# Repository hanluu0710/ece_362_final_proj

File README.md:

# ece_362_final_proj
Pocket oscilloscope

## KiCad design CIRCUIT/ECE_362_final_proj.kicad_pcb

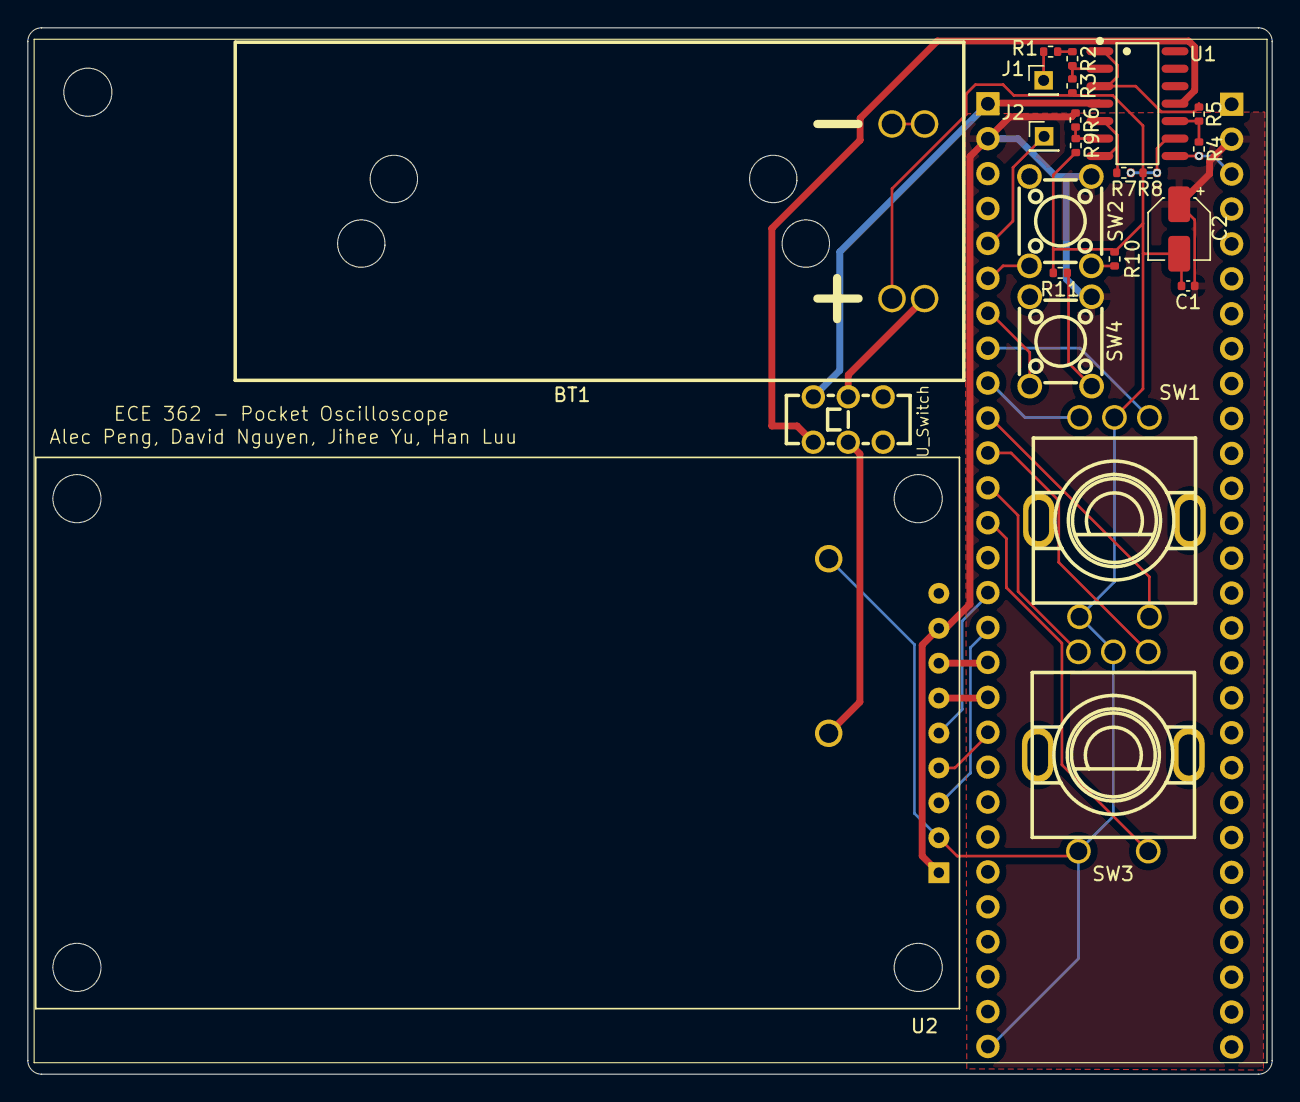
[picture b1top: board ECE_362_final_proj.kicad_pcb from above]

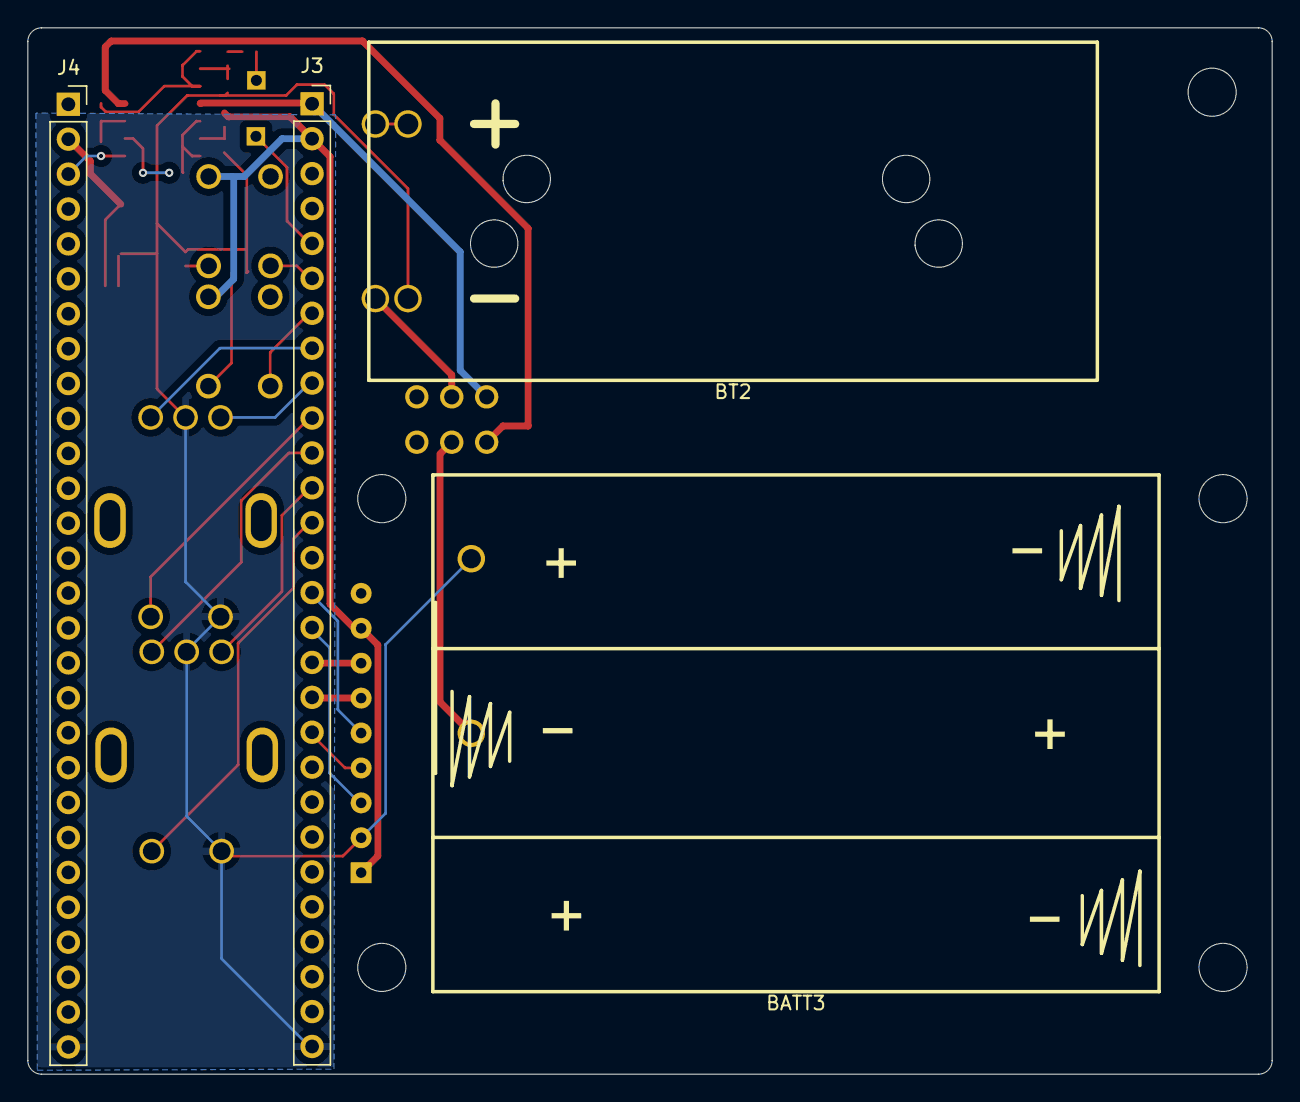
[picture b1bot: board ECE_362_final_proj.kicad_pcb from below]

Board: 2 copper layers, 90.5 x 76.1 mm, 27 parts (4 on the bottom side), 32 nets.

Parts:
BATT3: BAT-TH_2479
BT1, BT2: BAT-TH_2P-L53.0-W24.6-P12.70_2468
C1: .1uF; C_0402_1005Metric
C2: 10uF; CP_Elec_4x4.5
J1, J2: Conn_01x01_Pin; PinHeader_1x01_P2.00mm_Vertical
J3, J4: Conn_01x28_Socket; PinSocket_1x28_P2.54mm_Vertical
R1: 680k; R_0402_1005Metric
R2: 220k; R_0402_1005Metric
R3: 100k; R_0402_1005Metric
R4, R5, R6, R7, R8, R9: 10k; R_0402_1005Metric
R10, R11: 1000; R_0402_1005Metric
SW1, SW3: SW-TH_EC11E18244A5
SW2: BUTTON_MODE; SW-TH_4P-L6.0-W6.0-P4.50-LS6.5
SW4: BUTTON_CAPTURE; SW-TH_4P-L6.0-W6.0-P4.50-LS6.5
U1: TL084; SOP-14_L8.6-W3.9-P1.27-LS6.0-BL
U2: LCD_MSP2202_without_sd
U_Switch: SW-TH_SSSS222700

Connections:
+3.3V: C1.1, C2.1, J3.2, J4.2, R6.1, SW2.4 (A), SW4.4 (A), U2.1, U2.8
+BATT: J3.1, J4.1, U1.4 (V+), U_Switch.1
-BATT: U1.11 (V-), U_Switch.4
/GPIO2: J2.1, J3.5
/GPIO3: J3.6, SW2.1
/GPIO4: J3.7, SW4.1
/GPIO5: J3.8, SW1.A
/GPIO6: J3.9, SW1.B
/GPIO7: J3.10, SW1.D
/GPIO8: J3.11, SW3.A
/GPIO9: J3.12, SW3.B
/GPIO10: J3.13, SW3.D
/GPIO12: J3.15, U2.5
/GPIO13: J3.16, U2.3
/GPIO14: J3.17, U2.7
/GPIO15: J3.18, U2.6
/GPIO16: J3.19, U2.4
/GPIO47_ADC7: J4.3, R4.2, U1.8
BAT3: BATT3.2, U_Switch.5
BT1+: BT1.2, U_Switch.2
BT1_GND: BT1.1, BT2.2
GND: BATT3.1, BT2.1, C1.2, C2.2, J3.28, J4.28, R3.2, R8.2, R9.2, R10.2, R11.2, SW1.C, SW1.E, SW3.C, SW3.E, U2.2
unnamed: J1.1, R1.1
unnamed: R1.2, R2.1
unnamed: R10.1, SW2.3 (K)
unnamed: R11.1, SW4.3 (K)
unnamed: R5.1, U1.1, U1.3 (+)
unnamed: R2.2, R3.1, U1.2 (-)
unnamed: R7.2, U1.5 (+), U1.7
unnamed: R6.2, R9.1, U1.6 (-)
unnamed: R4.1, R5.2, U1.10 (+)
unnamed: R7.1, R8.1, U1.9 (-)

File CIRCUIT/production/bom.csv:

Designator,Footprint,Quantity,Value,LCSC Part #,Customer Supply
,,1,,,
BATT3,BAT-TH_2479,1,BAT-TH_2479,,
"BT1, BT2",BAT-TH_2P-L53.0-W24.6-P12.70_2468,2,BAT-TH_2P-L53.0-W24.6-P12.70_2468,,
C1,0402,1,.1uF,,
C2,CP_Elec_4x4.5,1,10uF,,
"J1, J2",PinHeader_1x01_P2.00mm_Vertical,2,Conn_01x01_Pin,,
"J3, J4",PinSocket_1x28_P2.54mm_Vertical,2,Conn_01x28_Socket,,
R1,0402,1,680k,,
"R10, R11",0402,2,1000,,
R2,0402,1,220k,,
R3,0402,1,100k,,
"R4, R5, R6, R7, R8, R9",0402,6,10k,,
"SW1, SW3",SW-TH_EC11E18244A5,2,~,,
SW2,SW-TH_4P-L6.0-W6.0-P4.50-LS6.5,1,BUTTON_MODE,,
SW4,SW-TH_4P-L6.0-W6.0-P4.50-LS6.5,1,BUTTON_CAPTURE,,
U1,SOP-14_L8.6-W3.9-P1.27-LS6.0-BL,1,TL084,,
U2,LCD_MSP2202_without_sd,1,LCD_MSP2202_without_sd,,DNP
U_SWITCH,SW-TH_SSSS222700,1,SW-TH_SSSS222700,,

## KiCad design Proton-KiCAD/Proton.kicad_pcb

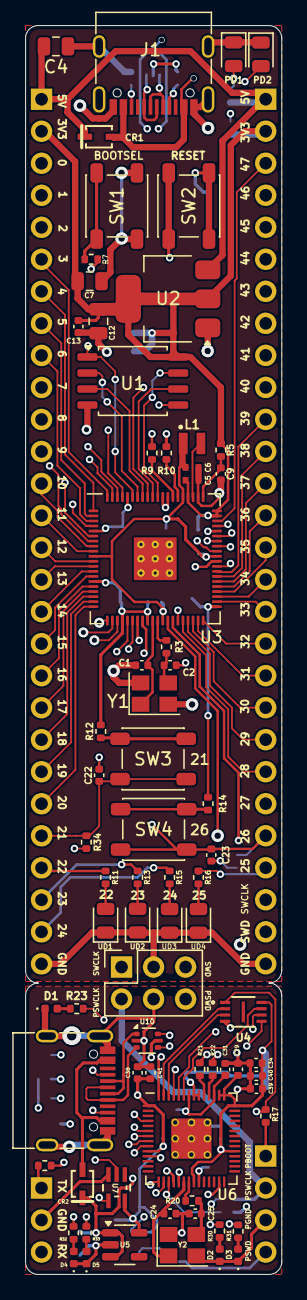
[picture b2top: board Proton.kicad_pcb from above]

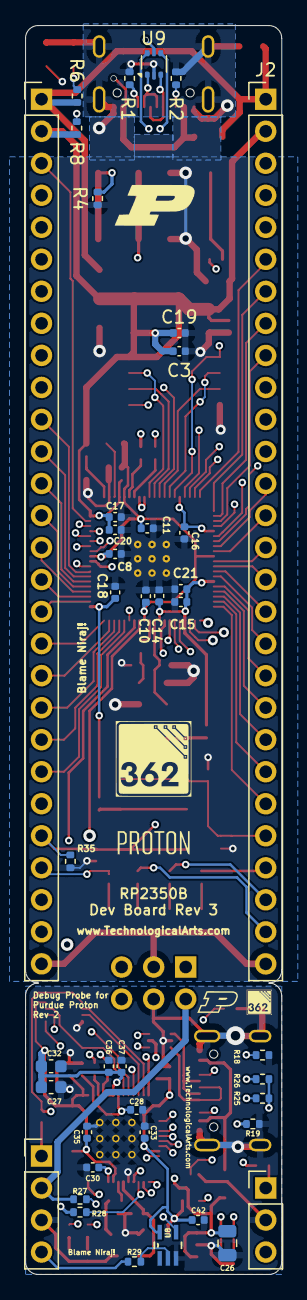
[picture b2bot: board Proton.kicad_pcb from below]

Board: 4 copper layers, 20.3 x 99.1 mm, 114 parts (41 on the bottom side), 130 nets.

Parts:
C1, C2, C24, C25: 15p; C_0402_1005Metric
C3, C8, C11, C13, C14, C15, C16, C17, C18, C19, C20, C21, C22, C23, C28, C29, C30, C33, C35, C36, C37, C38, C39, C40, C41, C42: 100n; C_0402_1005Metric
C4, C7, C12, C26: 10u; C_0805_2012Metric
C5, C6: 4.7u; C_0402_1005Metric_small_pads
C9, C10: 4.7u; C_0402_1005Metric
C27, C32: 10u; C_0603_1608Metric
C31, C34: 1u; C_0402_1005Metric
CR1, CR2: BAT60JFILM; CR_60JFILM_STM
D1: RED; D_0402_1005Metric
D2, D4: GREEN; D_0402_1005Metric
D3, D5: YELLOW; D_0402_1005Metric
J1, J5: USB_C_Receptacle_USB2.0_14P; USB_C_Receptacle_G-Switch_GT-USB-7010ASV
J2, J4: Conn_01x28_Pin; PinHeader_1x28_P2.54mm_Vertical
J3: DebugnBoot; PinHeader_1x04_P2.54mm_Vertical
J6: Conn_02x03_Top_Bottom; PinSocket_2x03_P2.54mm_Vertical
J7: UART-PINS; PinHeader_1x03_P2.54mm_Vertical
L1: 3.3u; L_pol_2016
PD1: RED; LED_0805_2012Metric
PD2: GREEN; LED_0805_2012Metric
R1, R2, R6, R18, R19: 5.1k; R_0402_1005Metric
R3, R4, R7, R8, R12, R14, R15, R17, R20: 1k; R_0402_1005Metric
R5: 33; R_0402_1005Metric
R9, R10, R21, R22: 27; R_0402_1005Metric
R11: 3k; R_0402_1005Metric
R13, R30, R32: 2k; R_0402_1005Metric
R16: 510; R_0402_1005Metric
R23, R31, R33: 470; R_0402_1005Metric
R24, R25, R26, R27, R28, R29: 100; R_0402_1005Metric
R34, R35: 10k; R_0402_1005Metric
SW1: BOOTSEL; SW_SPST_PTS647_Sx38
SW2: RESET; SW_SPST_PTS647_Sx38
SW3: LEFT; SW_SPST_PTS647_Sx38
SW4: RIGHT; SW_SPST_PTS647_Sx38
U1: W25Q128JVS; SOIC-8_5.23x5.23mm_P1.27mm
U2: NCP1117-3.3_SOT223; SOT-223-3_TabPin2
U3: RP2350_80QFN; RP2350-QFN-80-1EP_10x10_P0.4mm_EP3.4x3.4mm_ThermalVias
U4: W25Q16JVUXIQ TR; USON-8_UX_2x3x0p6_WIN
U5: AP2112K-3.3; SOT-23-5
U6: RP2040; RP2040-QFN-56
U7, U8: SN74AUP1T17DCKR; DCK5
U9, U10: USBLC6-2P6; SOT-666
UD1: RED; LED_0805_2012Metric
UD2: YELLOW; LED_0805_2012Metric
UD3: GREEN; LED_0805_2012Metric
UD4: BLUE; LED_0805_2012Metric
Y1, Y2: ABM8-272-T3; Crystal_SMD_3225-4Pin_3.2x2.5mm

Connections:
+1V1: C6.1, C8.1, C10.1, C11.1, L1.1, U3.10 (DVDD), U3.32 (DVDD), U3.51 (DVDD), U3.65 (VREG_FB)
+3V3: C3.1, C5.1, C7.1, C12.1, C13.1, C14.1, C15.1, C16.1, C17.1, C18.1, C19.1, C20.1, C21.1, J2.2, J4.2, R5.1, R8.1, R12.1, R14.1, U1.8 (VCC), U2.2 (VO), U3.5 (IOVDD), U3.15 (IOVDD), U3.24 (IOVDD), U3.29 (IOVDD), U3.41 (IOVDD), U3.50 (IOVDD), U3.59 (ADC_AVDD), U3.60 (IOVDD), U3.64 (VREG_VIN), U3.68 (USB_OTP_VDD), U3.69 (QSPI_IOVDD), U3.76 (IOVDD)
+P1V1: C28.1, C30.1, C31.1, U6.23 (DVDD), U6.45 (VREG_VOUT), U6.50 (DVDD)
+P3V3: C27.1, C29.1, C32.1, C33.1, C34.1, C35.1, C36.1, C37.1, C38.1, C39.1, C40.1, C41.1, C42.1, U4.8 (VCC), U5.5 (VOUT), U6.1 (IOVDD), U6.10 (IOVDD), U6.22 (IOVDD), U6.33 (IOVDD), U6.42 (IOVDD), U6.43 (ADC_AVDD), U6.44 (VREG_IN), U6.48 (USB_VDD), U6.49 (IOVDD), U7.5 (VCC), U8.5 (VCC)
/DebugProbe/GPIO2: R23.1, U6.4 (GPIO2)
/DebugProbe/GPIO4: R24.1, U6.6 (GPIO4)
/DebugProbe/GPIO5: U6.7 (GPIO5), U7.4 (Y)
/DebugProbe/GPIO6: R25.1, U6.8 (GPIO6)
/DebugProbe/GPIO7: R30.1, U6.9 (GPIO7)
/DebugProbe/GPIO8: R31.1, U6.11 (GPIO8)
/DebugProbe/GPIO12: R27.1, U6.15 (GPIO12)
/DebugProbe/GPIO13: U6.16 (GPIO13), U8.4 (Y)
/DebugProbe/GPIO14: R28.1, U6.17 (GPIO14)
/DebugProbe/GPIO15: R32.1, U6.18 (GPIO15)
/DebugProbe/GPIO16: R33.1, U6.27 (GPIO16)
/DebugProbe/QSPI_SCLK: U4.6 (CLK), U6.52 (QSPI_SCLK)
/DebugProbe/QSPI_SD0: U4.5 (DI(IO0)), U6.53 (QSPI_SD0)
/DebugProbe/QSPI_SD1: U4.2 (DO(IO1)), U6.55 (QSPI_SD1)
/DebugProbe/QSPI_SD2: U4.3 (/WP(IO2)), U6.54 (QSPI_SD2)
/DebugProbe/QSPI_SD3: U4.7 (/HOLDOR/RESET(IO3)), U6.51 (QSPI_SD3)
/DebugProbe/QSPI_SS: R17.1, U4.1 (/CS), U6.56 (QSPI_SS)
/DebugProbe/USB_D+: R21.1, U10.4 (I/O2)
/DebugProbe/USB_D-: R22.1, U10.6 (I/O1)
/DebugProbe/XIN: C24.1, U6.20 (XIN), Y2.1
/DebugProbe/XOUT: R20.1, U6.21 (XOUT)
/DebugProbe/~USB_BOOT: J3.1, R17.2
/FLASH_SS: R7.1, U1.1 (~CS), U3.75 (QSPI_SS)
/GPIO0: J2.3, U3.77 (GPIO0)
/GPIO1: J2.4, U3.78 (GPIO1)
/GPIO2: J2.5, U3.79 (GPIO2)
/GPIO3: J2.6, U3.80 (GPIO3)
/GPIO4: J2.7, U3.1 (GPIO4)
/GPIO5: J2.8, U3.2 (GPIO5)
/GPIO6: J2.9, U3.3 (GPIO6)
/GPIO7: J2.10, U3.4 (GPIO7)
/GPIO8: J2.11, U3.6 (GPIO8)
/GPIO9: J2.12, U3.7 (GPIO9)
/GPIO10: J2.13, U3.8 (GPIO10)
/GPIO11: J2.14, U3.9 (GPIO11)
/GPIO12: J2.15, U3.11 (GPIO12)
/GPIO13: J2.16, U3.12 (GPIO13)
/GPIO14: J2.17, U3.13 (GPIO14)
/GPIO15: J2.18, U3.14 (GPIO15)
/GPIO16: J2.19, U3.16 (GPIO16)
/GPIO17: J2.20, U3.17 (GPIO17)
/GPIO18: J2.21, U3.18 (GPIO18)
/GPIO19: J2.22, U3.19 (GPIO19)
/GPIO20: J2.23, U3.20 (GPIO20)
/GPIO21: C22.1, J2.24, R34.2, SW3.2, U3.21 (GPIO21)
/GPIO22: J2.25, R11.1, U3.22 (GPIO22)
/GPIO23: J2.26, R13.1, U3.23 (GPIO23)
/GPIO24: J2.27, R15.1, U3.25 (GPIO24)
/GPIO25: J4.25, R16.1, U3.26 (GPIO25)
/GPIO26: C23.1, J4.24, R35.2, SW4.2, U3.27 (GPIO26)
/GPIO27: J4.23, U3.28 (GPIO27)
/GPIO28: J4.22, U3.36 (GPIO28)
/GPIO29: J4.21, U3.37 (GPIO29)
/GPIO30: J4.20, U3.38 (GPIO30)
/GPIO31: J4.19, U3.39 (GPIO31)
/GPIO32: J4.18, U3.40 (GPIO32)
/GPIO33: J4.17, U3.42 (GPIO33)
/GPIO34: J4.16, U3.43 (GPIO34)
/GPIO35: J4.15, U3.44 (GPIO35)
/GPIO36: J4.14, U3.45 (GPIO36)
/GPIO37: J4.13, U3.46 (GPIO37)
/GPIO38: J4.12, U3.47 (GPIO38)
/GPIO39: J4.11, U3.48 (GPIO39)
/GPIO40_ADC0: J4.10, U3.49 (GPIO40_ADC0)
/GPIO41_ADC1: J4.9, U3.52 (GPIO41_ADC1)
/GPIO42_ADC2: J4.8, U3.53 (GPIO42_ADC2)
/GPIO43_ADC3: J4.7, U3.54 (GPIO43_ADC3)
/GPIO44_ADC4: J4.6, U3.55 (GPIO44_ADC4)
/GPIO45_ADC5: J4.5, U3.56 (GPIO45_ADC5)
/GPIO46_ADC6: J4.4, U3.57 (GPIO46_ADC6)
/GPIO47_ADC7: J4.3, U3.58 (GPIO47_ADC7)
/QSPI_SCLK: U1.6 (CLK), U3.71 (QSPI_SCLK)
/QSPI_SD0: U1.5 (DI(IO0)), U3.72 (QSPI_SD0)
/QSPI_SD1: U1.2 (DO(IO1)), U3.74 (QSPI_SD1)
/QSPI_SD2: U1.3 (IO2), U3.73 (QSPI_SD2)
/QSPI_SD3: U1.7 (IO3), U3.70 (QSPI_SD3)
/RUN: SW2.2, U3.35 (RUN)
/SWCLK: J4.26, J6.1, U3.33 (SWCLK)
/SWD: J4.27, J6.5, U3.34 (SWD)
/USB_D+: R9.1, U9.4 (I/O2)
/USB_D-: R10.1, U9.6 (I/O1)
/VREG_AVDD: C9.1, R5.2, U3.61 (VREG_AVDD)
/VREG_LX: L1.2, U3.63 (VREG_LX)
/XIN: C1.1, U3.30 (XIN), Y1.1
/XOUT: R3.1, U3.31 (XOUT)
/~USB_BOOT: R7.2, SW1.2
GND: C1.2, C2.2, C3.2, C4.2, C5.2, C6.2, C7.2, C8.2, C9.2, C10.2, C11.2, C12.2, C13.2, C14.2, C15.2, C16.2, C17.2, C18.2, C19.2, C20.2, C21.2, C22.2, C23.2, J1.A1 (GND), J1.A12 (GND), J1.B1 (GND), J1.B12 (GND), J1.S1 (SHIELD), J2.28, J4.28, J6.3, PD1.1 (K), PD2.1 (K), R1.2, R2.2, R4.2, R34.1, R35.1, SW1.1, U1.4 (GND), U2.1 (GND), U3.62 (VREG_PGND), U3.81 (GND), U9.2 (GND), UD1.1 (K), UD2.1 (K), UD3.1 (K), UD4.1 (K), Y1.2, Y1.4
unnamed: C2.1, R3.2, Y1.3
unnamed: C25.1, R20.2, Y2.3
unnamed: CR2.2, J5.A4 (VBUS), J5.A9 (VBUS), J5.B4 (VBUS), J5.B9 (VBUS)
unnamed: D1.2 (A), R23.2
unnamed: D2.2 (A), R30.2
unnamed: D3.2 (A), R31.2
unnamed: D4.2 (A), R32.2
unnamed: D5.2 (A), R33.2
unnamed: J1.A5 (CC1), R1.1
unnamed: J1.B5 (CC2), R2.1
unnamed: J1.A6 (D+), J1.B6 (D+), U9.3 (I/O2)
unnamed: J1.A7 (D-), J1.B7 (D-), U9.1 (I/O1)
unnamed: J5.A5 (CC1), R18.1
unnamed: J5.B5 (CC2), R19.1
unnamed: J5.A6 (D+), J5.B6 (D+), U10.3 (I/O2)
unnamed: J5.A7 (D-), J5.B7 (D-), U10.1 (I/O1)
unnamed: J7.1, R24.2
unnamed: J7.3, R25.2, R26.2
unnamed: PD1.2 (A), R6.2
unnamed: PD2.2 (A), R8.2
unnamed: R4.1, SW2.1
unnamed: R12.2, SW3.1
unnamed: R14.2, SW4.1
unnamed: R10.2, U3.66 (USB_DM)
unnamed: R9.2, U3.67 (USB_DP)
unnamed: R22.2, U6.46 (USB_DM)
unnamed: R21.2, U6.47 (USB_DP)
unnamed: R26.1, U7.2 (A)
unnamed: R29.1, U8.2 (A)
unnamed: R11.2, UD1.2 (A)
unnamed: R13.2, UD2.2 (A)
unnamed: R15.2, UD3.2 (A)
unnamed: R16.2, UD4.2 (A)
PGND: C24.2, C25.2, C26.2, C27.2, C28.2, C29.2, C30.2, C31.2, C32.2, C33.2, C34.2, C35.2, C36.2, C37.2, C38.2, C39.2, C40.2, C41.2, C42.2, D1.1 (K), D2.1 (K), D3.1 (K), D4.1 (K), D5.1 (K), J3.3, J5.A1 (GND), J5.A12 (GND), J5.B1 (GND), J5.B12 (GND), J5.S1 (SHIELD), J6.4, J7.2, R18.2, R19.2, U4.4 (GND), U5.2 (GND), U6.19 (TESTEN), U6.57 (GND), U7.3 (GND), U8.3 (GND), U10.2 (GND), Y2.2, Y2.4
PSWCLK: J3.2, J6.2, R27.2
PSWD: J3.4, J6.6, R28.2, R29.2
P_VBUS: C26.1, CR2.1, U5.1 (VIN), U5.3 (EN), U10.5 (VBUS)
UVBUS: CR1.2, J1.A4 (VBUS), J1.A9 (VBUS), J1.B4 (VBUS), J1.B9 (VBUS), U9.5 (VBUS)
VBUS: C4.1, CR1.1, J2.1, J4.1, R6.1, U2.3 (VI)

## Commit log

2025-11-07 init_spi
2025-11-07 chardisp init, spi_cmd, spi_data
2025-11-11 David's GPIO parts
2025-11-14 button and rotary encoder sch upload
2025-11-14 added a few comments and changed filename
2025-11-14 removed old file
2025-11-14 grid and div
2025-11-14 combined circuit
2025-11-15 There is still a debouncing issue with the rotary, but I GOT IT TO DECREASE KDJFSFHSGJSFGSJVVFH
2025-11-15 Add wavegen.h header for waveform generation
2025-11-18 Totally forgot abt the offset shifting, so I added that in
2025-11-18 PCB lowkey done
2025-11-18 added mounting holes
2025-11-18 rearranged board
2025-11-18 clean up folder
2025-11-18 adjusted trace width
2025-11-19 adjusted silkscreen
2025-11-19 adjusted signal window size
2025-11-20 PCB DONE
2025-11-26 file clean up
2025-11-26 fixed display scroll mode
2025-11-27 still trying to relate adc to pixel
2025-11-27 made scaling indepdent
2025-11-28 done integrating shift and scale Y. done integrating scale X. DITCH shift X
2025-11-28 cleaned up warnings
2025-11-28 capture is ACTIVATED
2025-11-28 capture and mode buttons might be floating, added a modified version for cross checking
2025-11-28 this will pause but will not allow shift and scaling after pause
2025-11-28 previous code has overlapping interrupt, this should work but still no zooming when paused though
2025-11-28 Change WAVEGEN_H directive from #ifdef to #ifndef
2025-11-28 Add PWM wave generation initialization
    Initialize PWM for wave generation with sine wave settings.
2025-11-28 Add wave generator with PWM control
    Implement wave generator functionality with PWM output.
2025-11-28 Remove oscilloscope initialization from main
    Removed call to run_oscilloscope() during initialization.
2025-11-28 ADC works
2025-12-01 works but cant relate wave period to displayed period
2025-12-01 I fixed some syntax errors and modified some codes in wavegen.c and wavegen.h
2025-12-01 removed freerun, changed buffsize
2025-12-08 final circuit
